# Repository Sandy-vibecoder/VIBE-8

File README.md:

<p align="center">

</p>

<p align="center">
  <b>8 LEDs · 1 header · any microcontroller</b><br>
  <a href="#ordering-the-pcb">Order the PCB</a> ·
  <a href="#pinout">Pinout</a> ·
  <a href="#example-code">Example code</a> ·
  <a href="docs/VIBE-8_schematic.pdf">Schematic (PDF)</a> ·
  <a href="fabrication/VIBE-8_v1.0_gerbers.zip">Gerbers (zip)</a>
</p>

---

**VIBE-8 v1.0** is a small 8-channel LED indicator board. Plug it into any microcontroller (Arduino, ESP32, Raspberry Pi Pico, ...) through one 10-pin header and you get eight LEDs you can switch on and off from code: status lights, a binary counter, a VU meter, or a light chaser.

It was designed in **KiCad 10** by **[Sandy-vibecoder](https://github.com/Sandy-vibecoder)** as a first PCB (18 Nov 2026).

| Front | Back |
|---|---|
|  |  |

---

## Table of contents

1. [Specifications](#specifications)
2. [How it works](#how-it-works)
3. [Pinout](#pinout)
4. [Bill of materials](#bill-of-materials)
5. [Ordering the PCB](#ordering-the-pcb)
6. [Assembly guide](#assembly-guide)
7. [Wiring it up](#wiring-it-up)
8. [Example code](#example-code)
9. [Design notes](#design-notes)
10. [Repository contents](#repository-contents)
11. [Opening and editing the design](#opening-and-editing-the-design)
12. [Version history](#version-history)

---

## Specifications

| Item | Value |
|---|---|
| Board size | **70 × 40 mm** (7 × 4 cm) |
| Assembled height | about 14 mm (about 9 mm of parts on top, about 3 mm of header pins below) |
| Copper layers | **2**: top = signal tracks, bottom = solid GND fill |
| Board thickness | 1.6 mm (standard) |
| Parts | All through-hole, easy to hand-solder |
| Channels | 8 independent LEDs |
| Logic | Active **HIGH**: a pin driven HIGH turns its LED on |
| Drive voltage | 3.3 V or 5 V logic |
| Current per LED | about 9 mA at 5 V, about 4 mA at 3.3 V (red LED, 330 Ω) |
| Total current, all 8 on | about 73 mA at 5 V |
| Holes | 44 plated holes (0.8 / 0.9 / 1.0 mm drills) |
| Mounting holes | None in v1.0 |
| Min. track / clearance | 0.5 mm / 0.25 mm |
| Design checks | ERC: 0 errors · DRC: 0 violations, 0 unconnected · board matches schematic |

---

## How it works

Each of the eight channels is the same simple circuit:

```
J2 pin n ──[ 330 Ω ]──►|── GND
 (signal)    R n      LED D n
```

- When your microcontroller drives a J2 signal pin **HIGH**, current flows through the resistor and the LED to ground, and the LED lights.
- When the pin is **LOW**, no current flows and the LED is off.
- The **330 Ω resistor** limits the current so neither the LED nor the microcontroller pin is damaged.
- All eight LED cathodes (−) share **GND**. The GND copper fill on the back of the board joins them.

**Power pins:** the **+5V** net on this board only connects **J1 pin 2** to **J2 pin 9**. No LED uses it. It's a pass-through, so you can power your microcontroller from J1 through the header, or bring 5 V out from the microcontroller. **GND** (J1 pin 1, J2 pin 10) is shared by the whole board and **must** be connected to your microcontroller's GND.

---

## Pinout

### J2 — 10-pin control header (2.54 mm)

Pin 1 has the **square pad**, at the left end when the LEDs face up.

| J2 pin | Signal | Function |
|---|---|---|
| 1 | LED1 | HIGH = D1 on |
| 2 | LED2 | HIGH = D2 on |
| 3 | LED3 | HIGH = D3 on |
| 4 | LED4 | HIGH = D4 on |
| 5 | LED5 | HIGH = D5 on |
| 6 | LED6 | HIGH = D6 on |
| 7 | LED7 | HIGH = D7 on |
| 8 | LED8 | HIGH = D8 on |
| 9 | +5V | Pass-through to J1 pin 2 (not used by the LEDs) |
| 10 | GND | Common ground (**required**) |

### J1 — 2-pin power header (2.54 mm)

| J1 pin | Signal |
|---|---|
| 1 (square pad) | GND |
| 2 | +5V |

The silkscreen next to the headers is printed `1-8: LEDs`, `5V GND` (J2) and `GND 5V` (J1) as a reminder.

---

## Bill of materials

Machine-readable version: [`bom/VIBE-8_BOM.csv`](bom/VIBE-8_BOM.csv)

| Reference | Qty | Value | Footprint | Notes |
|---|---|---|---|---|
| D1–D8 | 8 | LED, 5 mm | `LED_THT:LED_D5.0mm` | Any colour. Red/green/yellow are brightest at 3.3 V |
| R1–R8 | 8 | 330 Ω, 1/4 W | `Resistor_THT:R_Axial_DIN0207_L6.3mm_D2.5mm_P10.16mm_Horizontal` | Standard axial resistor |
| J2 | 1 | 1×10 male pin header, 2.54 mm | `Connector_PinHeader_2.54mm:PinHeader_1x10_P2.54mm_Vertical` | Snap from a 1×40 strip |
| J1 | 1 | 1×2 male pin header, 2.54 mm | `Connector_PinHeader_2.54mm:PinHeader_1x02_P2.54mm_Vertical` | Snap from the same strip |
| — | 1 | VIBE-8 PCB | — | See below |

---

## Ordering the PCB

1. Download [`fabrication/VIBE-8_v1.0_gerbers.zip`](fabrication/VIBE-8_v1.0_gerbers.zip). It contains only the Gerber and drill files, which is the format PCB factories want.
2. Upload it to a PCB service such as JLCPCB, PCBWay, OSH Park or Aisler.
3. The website should detect the board automatically. Check these settings:

| Setting | Choose |
|---|---|
| Layers | **2** |
| Dimensions | **70 × 40 mm** (should be detected) |
| Thickness | **1.6 mm** |
| Surface finish | HASL (cheapest) or ENIG (nicer) |
| Solder mask colour | Any you like |
| Quantity | 5 is the usual minimum |

4. Check the site's online preview: front, back, and the drill holes.

The individual Gerber files are also in [`fabrication/gerbers/`](fabrication/gerbers/):

| File | Layer |
|---|---|
| `Universal_LED_Module-F_Cu.gtl` | Top copper |
| `Universal_LED_Module-B_Cu.gbl` | Bottom copper (GND fill) |
| `Universal_LED_Module-F_Mask.gts` / `-B_Mask.gbs` | Solder mask, top / bottom |
| `Universal_LED_Module-F_Silkscreen.gto` / `-B_Silkscreen.gbo` | Silkscreen (white printing), top / bottom |
| `Universal_LED_Module-Edge_Cuts.gm1` | Board outline |
| `Universal_LED_Module.drl` | Drill file (Excellon) |
| `Universal_LED_Module-job.gbrjob` | Gerber job file (helps some fabs auto-detect settings) |

---

## Assembly guide

**Tools:** soldering iron, solder, side cutters.

Solder the **lowest parts first**, so the board sits flat on the table while you work:

1. **Resistors R1–R8.** Bend the legs, push them through, solder from the back, and trim the legs. Resistors have no polarity, so either direction works.
2. **LEDs D1–D8.** ⚠️ **Polarity matters.** The **short leg / flat side of the LED is the cathode (−)**. It goes into the **square pad** (the left pad of each LED, marked on the silkscreen). Solder one leg, check the LED sits straight, then solder the other.
3. **Pin headers J2 and J1.** Put the long pins on top. A trick: plug the header into a breadboard to hold it square while you solder.

**Test:** connect J2 pin 10 to GND and touch J2 pin 1 to 5 V (or 3.3 V). D1 should light. Repeat for pins 2–8.

---

## Wiring it up

Example: **Arduino Uno**

| VIBE-8 J2 | Arduino |
|---|---|
| 1 … 8 | D2 … D9 |
| 9 (+5V) | 5V *(optional)* |
| 10 (GND) | GND **(required)** |

Example: **ESP32 / Raspberry Pi Pico (3.3 V logic)** works the same way. Use any 8 free GPIO pins and connect GND. LEDs will be dimmer at 3.3 V (about 4 mA). Red, green and yellow LEDs work best; blue and white LEDs need a higher voltage and may barely light at 3.3 V with 330 Ω.

---

## Example code

### Arduino: light chaser

```cpp
// VIBE-8 light chaser
// J2 pins 1-8 -> Arduino D2-D9, J2 pin 10 -> GND
const int ledPins[8] = {2, 3, 4, 5, 6, 7, 8, 9};

void setup() {
  for (int i = 0; i < 8; i++) {
    pinMode(ledPins[i], OUTPUT);
  }
}

void loop() {
  for (int i = 0; i < 8; i++) {          // left to right
    digitalWrite(ledPins[i], HIGH);
    delay(80);
    digitalWrite(ledPins[i], LOW);
  }
  for (int i = 6; i > 0; i--) {          // and back
    digitalWrite(ledPins[i], HIGH);
    delay(80);
    digitalWrite(ledPins[i], LOW);
  }
}
```

### Arduino: 8-bit binary counter

```cpp
// Shows the numbers 0-255 in binary on the 8 LEDs (D1 = bit 0)
const int ledPins[8] = {2, 3, 4, 5, 6, 7, 8, 9};

void setup() {
  for (int i = 0; i < 8; i++) pinMode(ledPins[i], OUTPUT);
}

void loop() {
  for (int n = 0; n < 256; n++) {
    for (int bit = 0; bit < 8; bit++) {
      digitalWrite(ledPins[bit], (n >> bit) & 1);
    }
    delay(150);
  }
}
```

### MicroPython (Raspberry Pi Pico / ESP32)

```python
# VIBE-8 light chaser - change the GPIO numbers to match your wiring
# GP2-GP9 suit a Raspberry Pi Pico.
# On a classic ESP32, do NOT use GPIO 6-11 (wired to the flash chip);
# try e.g. (4, 13, 14, 25, 26, 27, 32, 33) instead.
from machine import Pin
import time

leds = [Pin(n, Pin.OUT) for n in (2, 3, 4, 5, 6, 7, 8, 9)]

while True:
    for led in leds:
        led.on()
        time.sleep(0.08)
        led.off()
```

---

## Design notes

- **Resistor value:** `R = (V_logic − V_LED) / I`. For a red LED (about 2.0 V) at 5 V: (5 − 2.0) / 330 Ω ≈ **9 mA**. That's bright, and well under the usual 20 mA per-pin limit of most microcontrollers. At 3.3 V: (3.3 − 2.0) / 330 Ω ≈ **4 mA**. For brighter LEDs at 3.3 V, use 150–220 Ω.
- **Layout:** each resistor sits directly under its LED's anode, so LED → resistor is a short straight track. The resistor → J2 tracks fan in like a funnel, middle channels first, so no tracks cross and no vias are needed.
- **Ground:** instead of nine GND tracks, the whole bottom copper layer is a GND fill. Every through-hole GND pad connects to it through thermal-relief spokes, which make soldering easier. The fill also helps shield against noise.
- **Track widths:** 0.5 mm with 0.25 mm clearance. That's generous for these small currents, and easy for any PCB factory to make.
- **Power flags:** PWR_FLAG symbols on +5V and GND tell KiCad's electrical rules checker where power enters the board.

### Ideas for v2

- Four M3 mounting holes in the corners
- An optional 74HC595 shift register, so all 8 LEDs need only 3 microcontroller pins
- SMD (0805) version for a smaller board

---

## Repository contents

```
VIBE-8/
├── README.md                     ← this file
├── kicad/                        ← KiCad 10 design files (open these to edit)
│   ├── Universal_LED_Module.kicad_pro
│   ├── Universal_LED_Module.kicad_sch   (schematic)
│   └── Universal_LED_Module.kicad_pcb   (PCB layout)
├── docs/
│   ├── vibe8-logo.svg            ← project logo
│   ├── VIBE-8_schematic.pdf      ← printable schematic
│   ├── VIBE-8_schematic.png
│   ├── VIBE-8_pcb_layout.pdf     ← layout: top copper, top silk, bottom copper, bottom silk
│   ├── VIBE-8_front.png          ← 3D render, front
│   └── VIBE-8_back.png           ← 3D render, back
├── bom/
│   └── VIBE-8_BOM.csv            ← bill of materials
└── fabrication/
    ├── VIBE-8_v1.0_gerbers.zip   ← upload this to the PCB factory
    └── gerbers/                  ← the same files, unzipped
```

---

## Opening and editing the design

1. Install [KiCad](https://www.kicad.org/) **10.0 or newer**.
2. Open `kicad/Universal_LED_Module.kicad_pro`.
3. The **Schematic Editor** shows the circuit, and the **PCB Editor** shows the board layout.
4. After making changes, run **Inspect → Electrical Rules Checker** (schematic) and **Inspect → Design Rules Checker** (PCB). Then regenerate the Gerbers with **File → Fabrication Outputs → Gerbers** and **Generate Drill Files**.

The KiCad project files are still named `Universal_LED_Module`, which was the working title. The board itself is VIBE-8.

---

## Version history

| Version | Date | Notes |
|---|---|---|
| v1.0 | 18 Nov 2026 | First design. 8 LEDs, 330 Ω, 2-layer, 70 × 40 mm. ERC/DRC clean. |

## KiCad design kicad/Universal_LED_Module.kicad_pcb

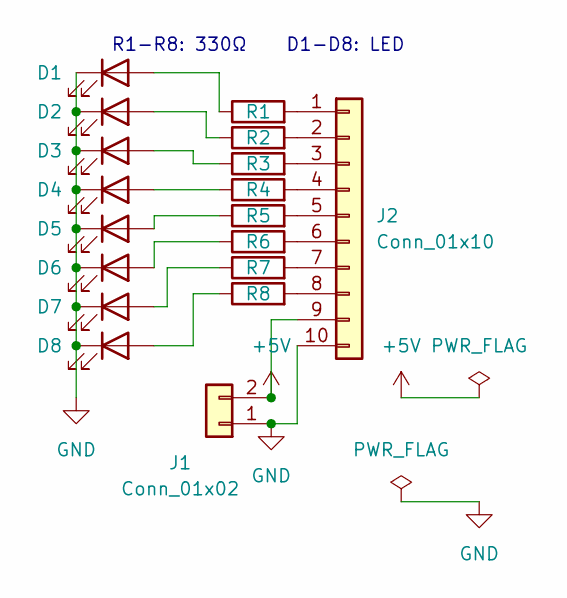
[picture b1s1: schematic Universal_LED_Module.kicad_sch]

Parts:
D1, D2, D3, D4, D5, D6, D7, D8: LED; LED_D5.0mm
J1: Conn_01x02; PinHeader_1x02_P2.54mm_Vertical
J2: Conn_01x10; PinHeader_1x10_P2.54mm_Vertical
R1, R2, R3, R4, R5, R6, R7, R8: 330; R_Axial_DIN0207_L6.3mm_D2.5mm_P10.16mm_Horizontal

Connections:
+5V: J1.2, J2.9
GND: D1.1 (K), D2.1 (K), D3.1 (K), D4.1 (K), D5.1 (K), D6.1 (K), D7.1 (K), D8.1 (K), J1.1, J2.10
unnamed: D1.2 (A), R1.1
unnamed: D2.2 (A), R2.1
unnamed: D3.2 (A), R3.1
unnamed: D4.2 (A), R4.1
unnamed: D5.2 (A), R5.1
unnamed: D6.2 (A), R6.1
unnamed: D7.2 (A), R7.1
unnamed: D8.2 (A), R8.1
unnamed: J2.1, R1.2
unnamed: J2.2, R2.2
unnamed: J2.3, R3.2
unnamed: J2.4, R4.2
unnamed: J2.5, R5.2
unnamed: J2.6, R6.2
unnamed: J2.7, R7.2
unnamed: J2.8, R8.2

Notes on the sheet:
R1-R8: 330Ω D1-D8: LED

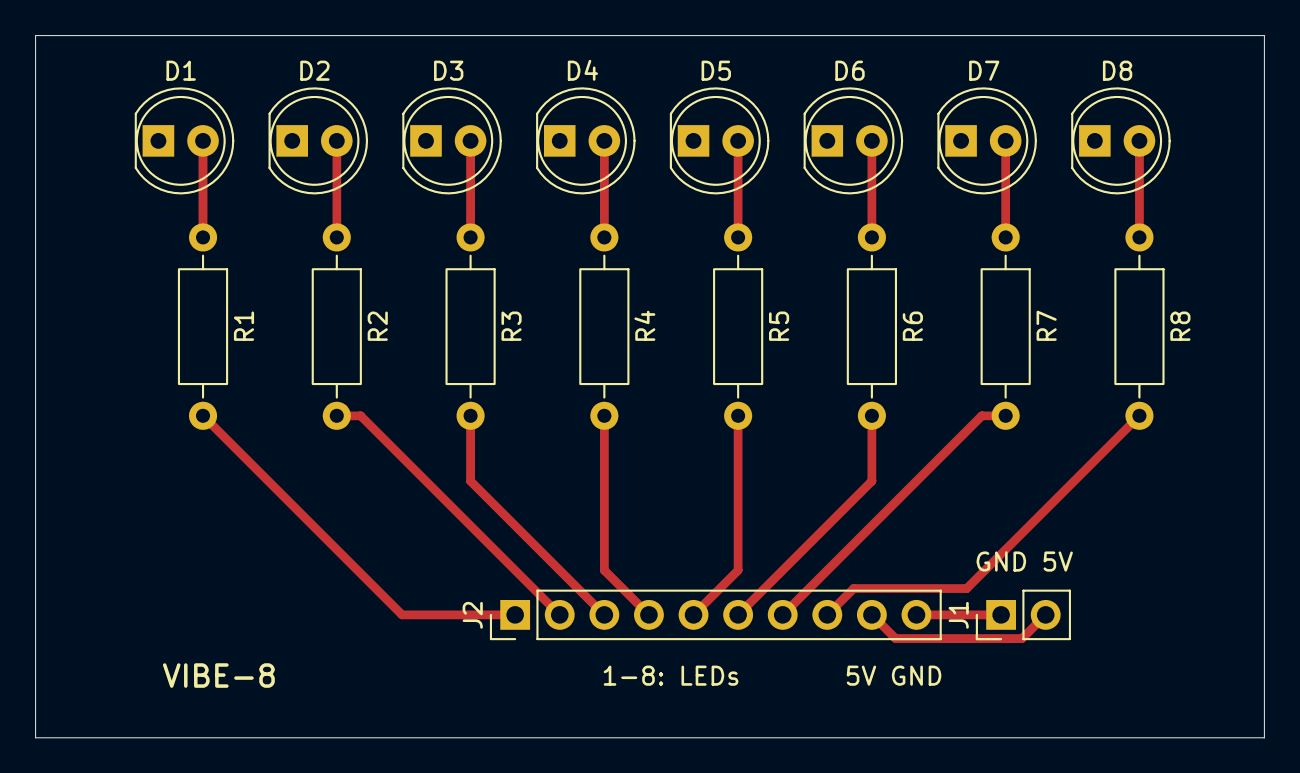
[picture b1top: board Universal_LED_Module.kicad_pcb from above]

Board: 2 copper layers, 70.0 x 40.0 mm, 18 parts (0 on the bottom side), 18 nets.

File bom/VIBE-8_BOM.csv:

"Reference","Value","Footprint","Qty"
"D1-D8","LED","LED_THT:LED_D5.0mm","8"
"J1","Conn_01x02","Connector_PinHeader_2.54mm:PinHeader_1x02_P2.54mm_Vertical","1"
"J2","Conn_01x10","Connector_PinHeader_2.54mm:PinHeader_1x10_P2.54mm_Vertical","1"
"R1-R8","330","Resistor_THT:R_Axial_DIN0207_L6.3mm_D2.5mm_P10.16mm_Horizontal","8"
